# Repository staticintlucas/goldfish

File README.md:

# Goldfish v2

> [!NOTE]\
> The main branch contains the design for Goldfish v2. The Goldfish v1 design is available in the [v1 branch](https://github.com/staticintlucas/goldfish/tree/v1)

Goldfish is a Pro Micro compatible microcontroller board designed for use in mechanical keyboards. It is based on the same Atmel ATMega32U4 chip and is programmable using the Arduino IDE or a keyboard specific firmware such as TMK or QMK. Of course it is perfectly usable for any other electronics projects too, not just keyboards.

## Links

- [PCB Source Files](cad)

- [Schematic](docs/schematic.pdf)

- [BOM](BOM.csv)

## Features

- Lower board profile with the mid-mounted USB-C connector
- Two internal pins make the USB data lines easily accessible
- USB-C is more durable, reversible and just plain cool
- 5 additional pins on the bottom edge of the board
- Pin-compatible with the original Pro Micro
- Sturdier through-hole USB connector
- On board ESD protection for USB lines

## Changes compared to Goldfish v1

- Addition of on board ESD protection and fuse
- All 0603 resistors and capacitors for (slightly) easier hand assembly
- Castellated edge connectors similar to the Elite-C
- Less obscure USB-C connector
  - Use of more commonly available components in 2022
  - Choice between multiple compatible connectors and suppliers
  - Uses USB 2.0-only connector for easier and cheaper assembly

## USB-C Connectors

| Manufacturer | Part number | | | |
|:--- |:---:|:---:|:---:|:---:|
| Molex | 216990-0001 | - | 216990-0003 | 216990-0002 |
| HRO | - | TYPE-C-31-M-13C | TYPE-C-31-M-13B | TYPE-C-31-M-13A |
| GCT | USB4520 | USB4510 | USB4505 | USB4500 |
| Approx. thickness<br>1.2 mm PCB | ![c21p12]<br>3.2 mm | ![c16p12]<br>3.2 mm | ![c10p12]<br>3.4 mm | ![c08p12]<br>3.6 mm |
| Approx. thickness<br>1.6 mm PCB | ![c21p16]<br>3.2 mm | ![c16p16]<br>3.2 mm | ![c10p16]<br>3.8 mm | ![c08p16]<br>4.0 mm |

[c21p12]: docs/connectors/conn-21-pcb-12.png
[c16p12]: docs/connectors/conn-16-pcb-12.png
[c10p12]: docs/connectors/conn-10-pcb-12.png
[c08p12]: docs/connectors/conn-08-pcb-12.png
[c21p16]: docs/connectors/conn-21-pcb-16.png
[c16p16]: docs/connectors/conn-16-pcb-16.png
[c10p16]: docs/connectors/conn-10-pcb-16.png
[c08p16]: docs/connectors/conn-08-pcb-16.png

## Limitations compared to a Pro Micro

- No onboard RX, TX LEDs
- No onboard voltage regulator (this makes no difference for keyboards; a regulator is only required when power supplies of over 5.5V are used)

## Vendors Selling Goldfish

#### Goldfish v1 rev. C

- [BeeKeeb]

#### Comet (modified design based on Goldfish v1; see related projects)

- [Tokas' Kable Works]

**Note:** These products are sold by 3rd party vendors and are not 'officially' endorsed by me. I'm simply listing them here for convenience.

[beekeeb]: https://shop.beekeeb.com/product/goldfish-rev-c-open-source-pro-micro-replacement/
[tokas' kable works]: https://shop.tokas.co.uk/product/comet-usb-c-microcontroller/

*(Also please let me know if anything is missing from this list)*

## Related Projects

#### [Alvaro] by Ariamelon

- A modified Goldfish v1 using 0603 components instead of 0402

#### [Comet] by Tokas

- A modified Goldfish v1 using a HRO TYPE-C-31-M-12 connector

#### [Whale] by Jia Geng Chang

- A modified Goldfish v1 using a Jing 918-418K2024S40000 connector

#### [Goldfish-clone-JLCPCB] by Jeremy J Starcher

- A modified Goldfish v1 designed to meet JLCPCB's assembly requirements

#### [Elite-C] from keeb.io

- An unrelated and closed source project with similar design goals

[alvaro]: https://github.com/Ariamelon/Alvaro
[comet]: https://github.com/vattern/comet
[whale]: https://github.com/JiaGengChang/Whale
[elite-c]: https://keeb.io/products/elite-c-low-profile-version-usb-c-pro-micro-replacement-atmega32u4
[goldfish-clone-jlcpcb]: https://github.com/JeremyJStarcher/Goldfish-clone-JLCPCB

*(Please let me know if anything is missing form this list)*

## License

Released under the Creative Commons Attribution Share-Alike 4.0 License.
https://creativecommons.org/licenses/by-sa/4.0/

Original Arduino Mini Design by Team Arduino.
Arduino Pro Mini Design by Spark Fun Electronics.
Pro Micro Design by Spark Fun Electronics.
Goldfish Design by Lucas Jansen.

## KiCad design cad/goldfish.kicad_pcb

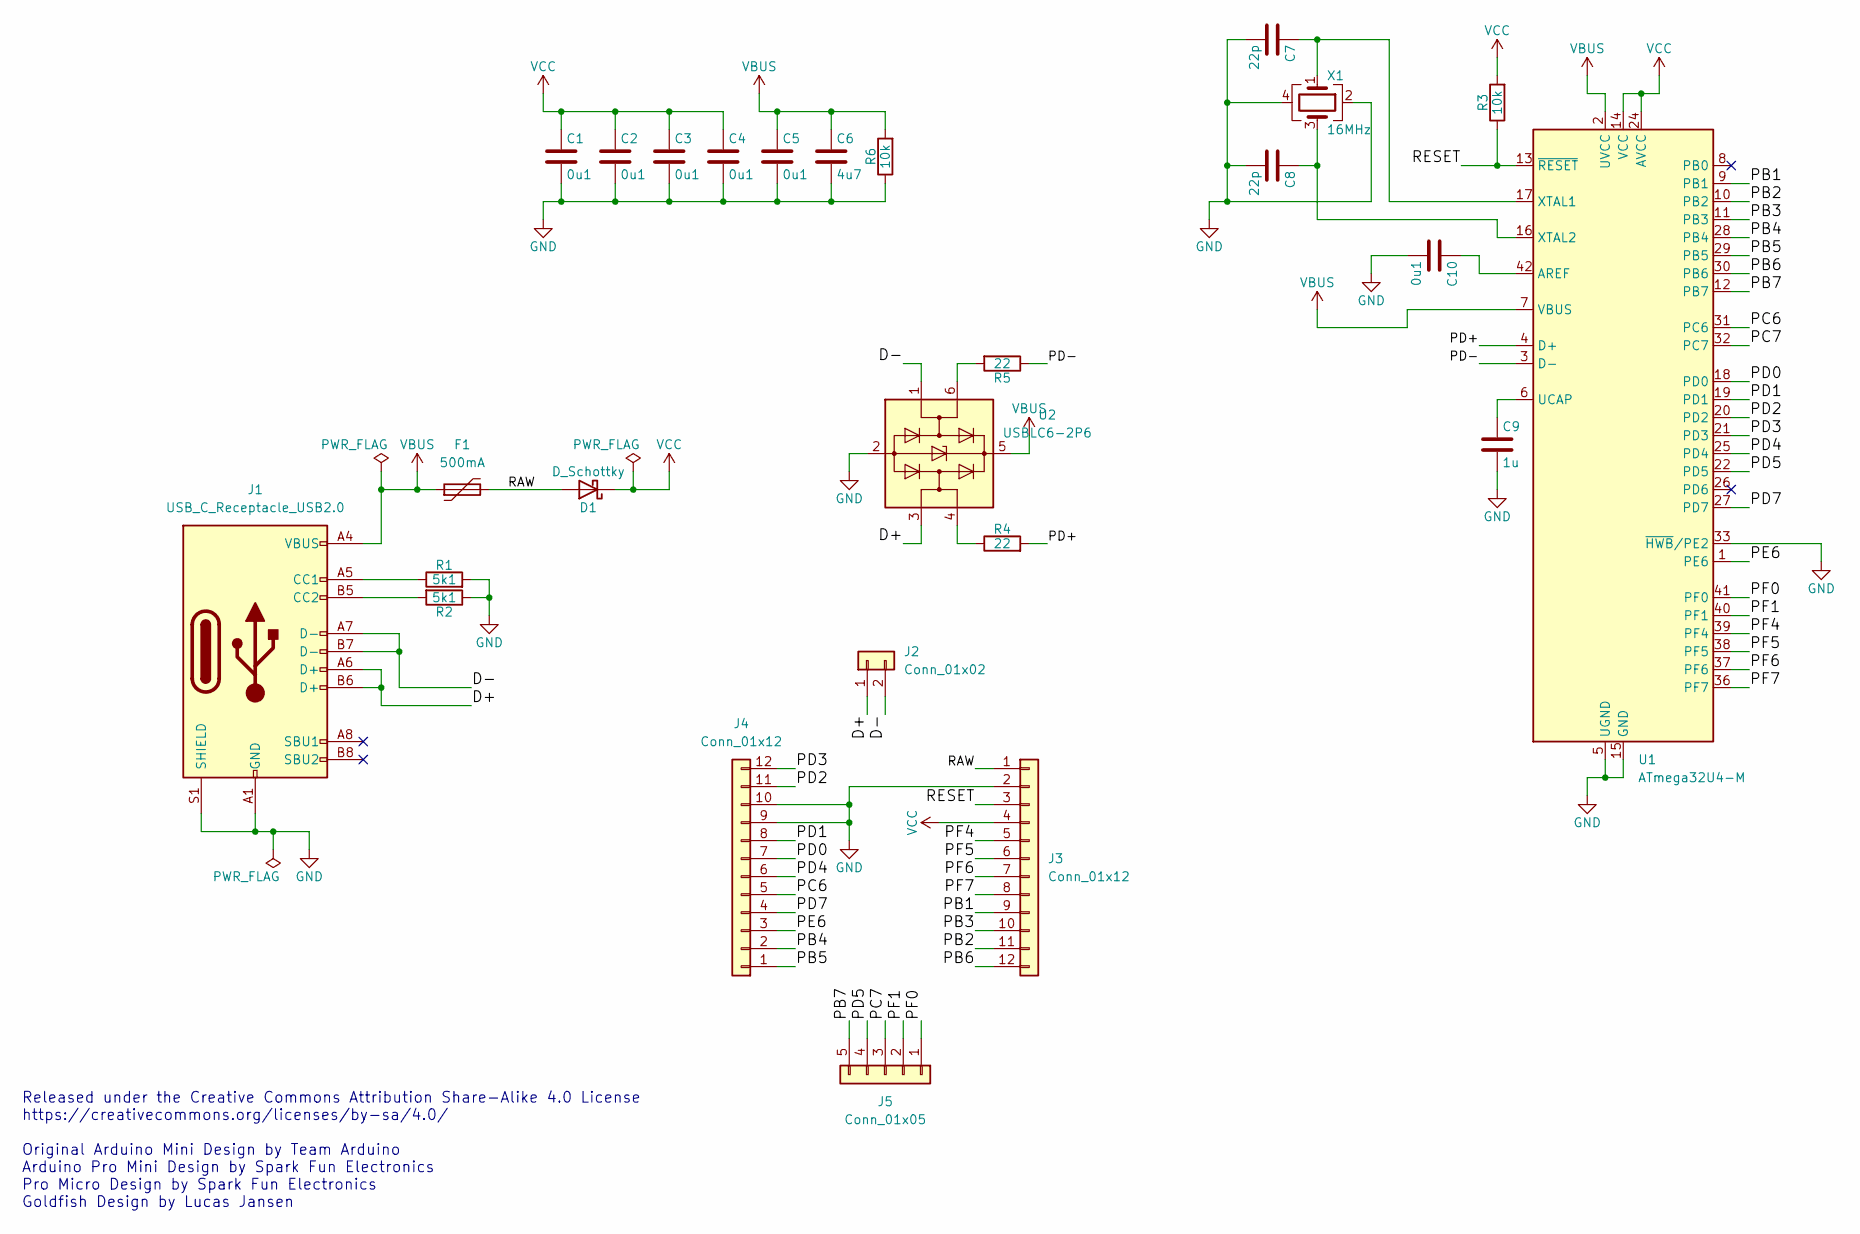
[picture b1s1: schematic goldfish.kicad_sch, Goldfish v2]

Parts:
C1, C2, C3, C4, C5, C10: 0u1; C_0603_1608Metric
C6: 4u7; C_0603_1608Metric
C7, C8: 22p; C_0603_1608Metric
C9: 1u; C_0603_1608Metric
D1: D_Schottky; D_SOD-123F
F1: 500mA; Fuse_0805_2012Metric
J1: USB_C_Receptacle_USB2.0; Molex-216990_GCT-USB45xx_HRO-TYPE-C-31-M-13x
J2: Conn_01x02; Pins_USB
J3, J4: Conn_01x12; Pins_x12_Castellated
J5: Conn_01x05; Pins_x05_Castellated
R1, R2: 5k1; R_0603_1608Metric
R3, R6: 10k; R_0603_1608Metric
R4, R5: 22; R_0603_1608Metric
U1: ATmega32U4-M; QFN-44-1EP_7x7mm_P0.5mm_EP5.2x5.2mm
U2: USBLC6-2P6; SOT-666
X1: 16MHz; Crystal_SMD_SeikoEpson_FA238-4Pin_3.2x2.5mm

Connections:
/D+: J1.A6 (D+), J1.B6 (D+), J2.1, U2.3 (I/O2)
/D-: J1.A7 (D-), J1.B7 (D-), J2.2, U2.1 (I/O1)
/PB1: J3.9, U1.9 (PB1)
/PB2: J3.11, U1.10 (PB2)
/PB3: J3.10, U1.11 (PB3)
/PB4: J4.2, U1.28 (PB4)
/PB5: J4.1, U1.29 (PB5)
/PB6: J3.12, U1.30 (PB6)
/PB7: J5.5, U1.12 (PB7)
/PC6: J4.5, U1.31 (PC6)
/PC7: J5.3, U1.32 (PC7)
/PD0: J4.7, U1.18 (PD0)
/PD1: J4.8, U1.19 (PD1)
/PD2: J4.11, U1.20 (PD2)
/PD3: J4.12, U1.21 (PD3)
/PD4: J4.6, U1.25 (PD4)
/PD5: J5.4, U1.22 (PD5)
/PD7: J4.4, U1.27 (PD7)
/PD+: R4.2, U1.4 (D+)
/PD-: R5.1, U1.3 (D-)
/PE6: J4.3, U1.1 (PE6)
/PF0: J5.1, U1.41 (PF0)
/PF1: J5.2, U1.40 (PF1)
/PF4: J3.5, U1.39 (PF4)
/PF5: J3.6, U1.38 (PF5)
/PF6: J3.7, U1.37 (PF6)
/PF7: J3.8, U1.36 (PF7)
/RAW: D1.2 (A), F1.2, J3.1
/RESET: J3.3, R3.1, U1.13 (~RESET)
GND: C1.2, C2.2, C3.2, C4.2, C5.2, C6.2, C7.2, C8.2, C9.2, C10.2, J1.A1 (GND), J1.A12 (GND), J1.B1 (GND), J1.B12 (GND), J1.S1 (SHIELD), J3.2, J4.9, J4.10, R1.2, R2.1, R6.1, U1.5 (UGND), U1.15 (GND), U1.23 (GND), U1.33 (~HWB/PE2), U1.35 (GND), U1.43 (GND), U1.45 (GND), U2.2 (GND), X1.2, X1.4
unnamed: C7.1, U1.17 (XTAL1), X1.1
unnamed: C8.1, U1.16 (XTAL2), X1.3
unnamed: C9.1, U1.6 (UCAP)
unnamed: C10.1, U1.42 (AREF)
unnamed: J1.A5 (CC1), R1.1
unnamed: J1.B5 (CC2), R2.2
unnamed: R4.1, U2.4 (I/O2)
unnamed: R5.2, U2.6 (I/O1)
VBUS: C5.1, C6.1, F1.1, J1.A4 (VBUS), J1.A9 (VBUS), J1.B4 (VBUS), J1.B9 (VBUS), R6.2, U1.2 (UVCC), U1.7 (VBUS), U2.5 (VBUS)
VCC: C1.1, C2.1, C3.1, C4.1, D1.1 (K), J3.4, R3.2, U1.14 (VCC), U1.24 (AVCC), U1.34 (VCC), U1.44 (AVCC)

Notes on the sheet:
Released under the Creative Commons Attribution Share-Alike 4.0 License https://creativecommons.org/licenses/by-sa/4.0/ Original Arduino Mini Design by Team Arduino Arduino Pro Mini Design by Spark Fun Electronics Pro Micro Design by Spark Fun Electronics Goldfish Design by Lucas Jansen

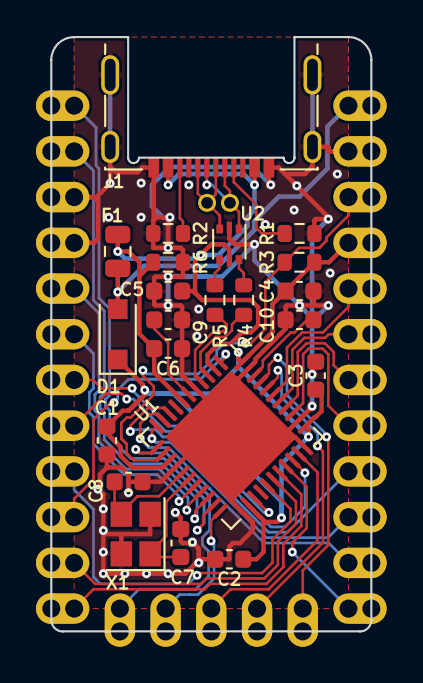
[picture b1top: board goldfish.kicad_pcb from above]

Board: 2 copper layers, 17.8 x 33.0 mm, 26 parts (0 on the bottom side), 40 nets.

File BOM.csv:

Item #,Designator,Quantity,Manufacturer,Part #,Value,Package,Type,Notes
1,"C1,C2,C3,C4,C5,C10",6,,,Cap 0u1 10%,0603,SMD,
2,C6,1,,,Cap 4u7 10%,0603,SMD,
3,"C7,C8",2,,,Cap 22p 5%,0603,SMD,
4,C9,1,,,Cap 1u 10%,0603,SMD,
5,D1,1,,,Schottky Diode 1A,SOD-123FL,SMD,
6,F1,1,,,Resettable Fuse 12V 500mA,0805,SMD,
7,J1,1,Molex,2169900001,USB 2.0 Type C Receptacle Mid Mount,,SMD/THT,
7,J1,1,GCT,USB4520-03-0-A,USB 2.0 Type C Receptacle Mid Mount,,SMD/THT,Alternate part for J1
7,J1,1,GCT,USB4520-03-1-A,USB 2.0 Type C Receptacle Mid Mount,,SMD/THT,Alternate part for J1
7,J1,1,GCT,USB4510-03-1-A,USB 2.0 Type C Receptacle Mid Mount,,SMD/THT,Alternate part for J1
7,J1,1,HRO,TYPE-C-31-M-13C,USB 2.0 Type C Receptacle Mid Mount,,SMD/THT,Alternate part for J1
7,J1,1,Molex,2169900003,USB 2.0 Type C Receptacle Mid Mount,,SMD/THT,Alternate part for J1
7,J1,1,GCT,USB4505-03-0-A,USB 2.0 Type C Receptacle Mid Mount,,SMD/THT,Alternate part for J1
7,J1,1,HRO,TYPE-C-31-M-13B,USB 2.0 Type C Receptacle Mid Mount,,SMD/THT,Alternate part for J1
7,J1,1,Molex,2169900002,USB 2.0 Type C Receptacle Mid Mount,,SMD/THT,Alternate part for J1
7,J1,1,GCT,USB4500-03-0-A,USB 2.0 Type C Receptacle Mid Mount,,SMD/THT,Alternate part for J1
7,J1,1,GCT,USB4500-03-1-A,USB 2.0 Type C Receptacle Mid Mount,,SMD/THT,Alternate part for J1
7,J1,1,HRO,TYPE-C-31-M-13A,USB 2.0 Type C Receptacle Mid Mount,,SMD/THT,Alternate part for J1
8,"R1,R2",2,,,Res 5k1 1%,0603,SMD,
9,"R3,R6",2,,,Res 10k 1%,0603,SMD,
10,"R4,R5",2,,,Res 22R 1%,0603,SMD,
11,U1,1,Microchip,ATmega32U4-MU,MCU 8-bit 16MHz 32K Flash,QFN44 7x7mm 0.5mm pitch,SMD,
12,U2,1,ST,USBLC6-2P6,ESD Suppression TVS Diodes,SOT-666,SMD,
13,X1,1,,,Crystal 16MHz 18pF,SMD3225 4P,SMD,

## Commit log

2018-01-05 Rev. 0 - Initial Design
2018-01-05 Fixed my bad markdown in the README.md
2018-01-05 Rev. A - Changed footprint of C6 from 0402 to 0603 to reduce component cost
2018-01-05 Still learning how to English good and formatting for the README.md
2018-01-07 Some small changes to the README
2018-01-07 Some small changes to the README again
2018-02-09 Rev. B - Fixed split keyboard issue and tidied up layout
2019-09-03 Rev. C - Changed bottom pins for Elite-C compatibility
2019-10-30 Fixed missing goldfish-rescue file error
2020-09-17 Fix formatting error in README.md
2021-03-09 Update README with link to Comet board
2021-03-10 Add more related projects to README
2021-03-10 Fix formatting in README
2021-12-25 Reworked README
2021-12-25 Apply suggestions from code review
2021-12-25 Applied **Requested** Changes
2021-12-25 Reworked README (#6)
    * Reworked README
    * Apply suggestions from code review
    * Applied **Requested** Changes
    * Delete fp-info-cache
2021-12-25 Reworked README (#6)
    * Reworked README
    * Apply suggestions from code review
    * Applied **Requested** Changes
    * Delete fp-info-cache
2022-05-15 Update README to include link to Whale microcontroller
2022-05-16 Punctuation changes in the README
2022-05-16 Update gitignore for latest Kicad versions
2022-05-23 Misc readme changes
2022-05-23 Mention silkscreen issue
2022-05-23 Fix typo
2022-05-24 Fix silkscreen on bottom edge pins
2022-05-24 Update README; change capitalisation of V1 Rev. X
2022-05-25 Add initial V2 design
2022-05-25 Update preview image and schematic PDF
2022-05-25 Update README for v2
2022-05-26 Update preview image
2022-05-27 Adjust USB-C connector 3D model position
2022-05-27 Adjust connector colours
2022-05-27 Add info about possible connectors to the README
2022-07-16 Misc README updates
2022-07-16 Switch D1 to SOD 123F
2022-07-16 Add BOM
2022-07-16 Forgot to recalculate ground pours
2022-07-16 v2 rev0 prerelease
2023-11-12 Add original artwork and connector models
2023-11-12 Update design files to KiCad 7
2023-11-12 Add .gitattributes for eol normalisation
